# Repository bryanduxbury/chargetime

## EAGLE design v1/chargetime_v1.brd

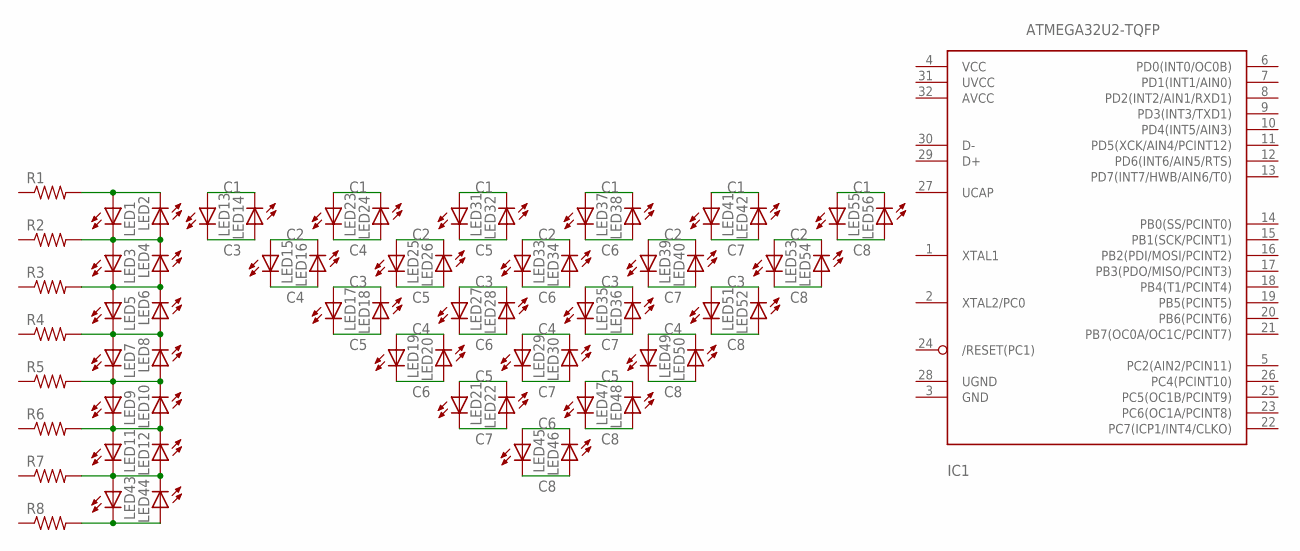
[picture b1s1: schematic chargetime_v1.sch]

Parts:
IC1: ATMEGA32U2-TQFP; TQFP32-08
LED1, LED2, LED3, LED4, LED5, LED6, LED7, LED8, LED9, LED10, LED11, LED12, LED13, LED14, LED15, LED16, LED17, LED18, LED19, LED20, LED21, LED22, LED23, LED24, LED25, LED26, LED27, LED28, LED29, LED30, LED31, LED32, LED33, LED34, LED35, LED36, LED37, LED38, LED39, LED40, LED41, LED42, LED43, LED44, LED45, LED46, LED47, LED48, LED49, LED50, LED51, LED52, LED53, LED54, LED55, LED56: LEDCHIPLED_1206; CHIPLED_1206
R1, R2, R3, R4, R5, R6, R7, R8: RESISTOR1206; 1206

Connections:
C1: LED1.A, LED2.C, LED13.A, LED14.C, LED23.A, LED24.C, LED31.A, LED32.C, LED37.A, LED38.C, LED41.A, LED42.C, LED55.A, LED56.C, R1.2
C2: LED1.C, LED2.A, LED3.A, LED4.C, LED15.A, LED16.C, LED25.A, LED26.C, LED33.A, LED34.C, LED39.A, LED40.C, LED53.A, LED54.C, R2.2
C3: LED3.C, LED4.A, LED5.A, LED6.C, LED13.C, LED14.A, LED17.A, LED18.C, LED27.A, LED28.C, LED35.A, LED36.C, LED51.A, LED52.C, R3.2
C4: LED5.C, LED6.A, LED7.A, LED8.C, LED15.C, LED16.A, LED19.A, LED20.C, LED23.C, LED24.A, LED29.A, LED30.C, LED49.A, LED50.C, R4.2
C5: LED7.C, LED8.A, LED9.A, LED10.C, LED17.C, LED18.A, LED21.A, LED22.C, LED25.C, LED26.A, LED31.C, LED32.A, LED47.A, LED48.C, R5.2
C6: LED9.C, LED10.A, LED11.A, LED12.C, LED19.C, LED20.A, LED27.C, LED28.A, LED33.C, LED34.A, LED37.C, LED38.A, LED45.A, LED46.C, R6.2
C7: LED11.C, LED12.A, LED21.C, LED22.A, LED29.C, LED30.A, LED35.C, LED36.A, LED39.C, LED40.A, LED41.C, LED42.A, LED43.A, LED44.C, R7.2
C8: LED43.C, LED44.A, LED45.C, LED46.A, LED47.C, LED48.A, LED49.C, LED50.A, LED51.C, LED52.A, LED53.C, LED54.A, LED55.C, LED56.A, R8.2

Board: 2 copper layers, 65 parts (0 on the bottom side), 8 nets, no tracks yet.

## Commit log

2013-06-09 wip of circuit board
2013-06-09 gitignore
2013-06-09 remove boring files
2013-06-09 add scadfile

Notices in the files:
parts and their libraries:
SparkFun: Licensing: CC v3.0 Share-Alike You are welcome to use this library for commercial purposes.
